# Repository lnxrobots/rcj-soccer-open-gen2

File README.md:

# RoboCup Soccer Open, Gen 2

## Setup

### Clone

Clone this repository in the home directory.

### Enable SSH and UART

Using `sudo raspi-config`

### Install packages and libraries

```
sudo apt install python3-pip git i2c-tools python3-opencv python3-serial python3-websockets
```

```
pip3 install bluedot
```

### Set cameras and optionally disable builtin Bluetooth

Add following lines to `/boot/firmware/config.txt`, change cameras if needed:

```
# Automatically load overlays for detected cameras
camera_auto_detect=0
dtoverlay=imx708,rotation=0,cam0
dtoverlay=imx477,cam1

# Uncomment to disable builtin bluetooth - custom
#dtoverlay=disable-bt
```

### Add launcher to autostart

Run `Launcher/apply_service.sh`.

### Pairing robots

Pair using [bluedot manual](https://bluedot.readthedocs.io/en/latest/pairpipi.html).

### Camera

Obtain frames using [Picamera2](https://github.com/raspberrypi/picamera2).

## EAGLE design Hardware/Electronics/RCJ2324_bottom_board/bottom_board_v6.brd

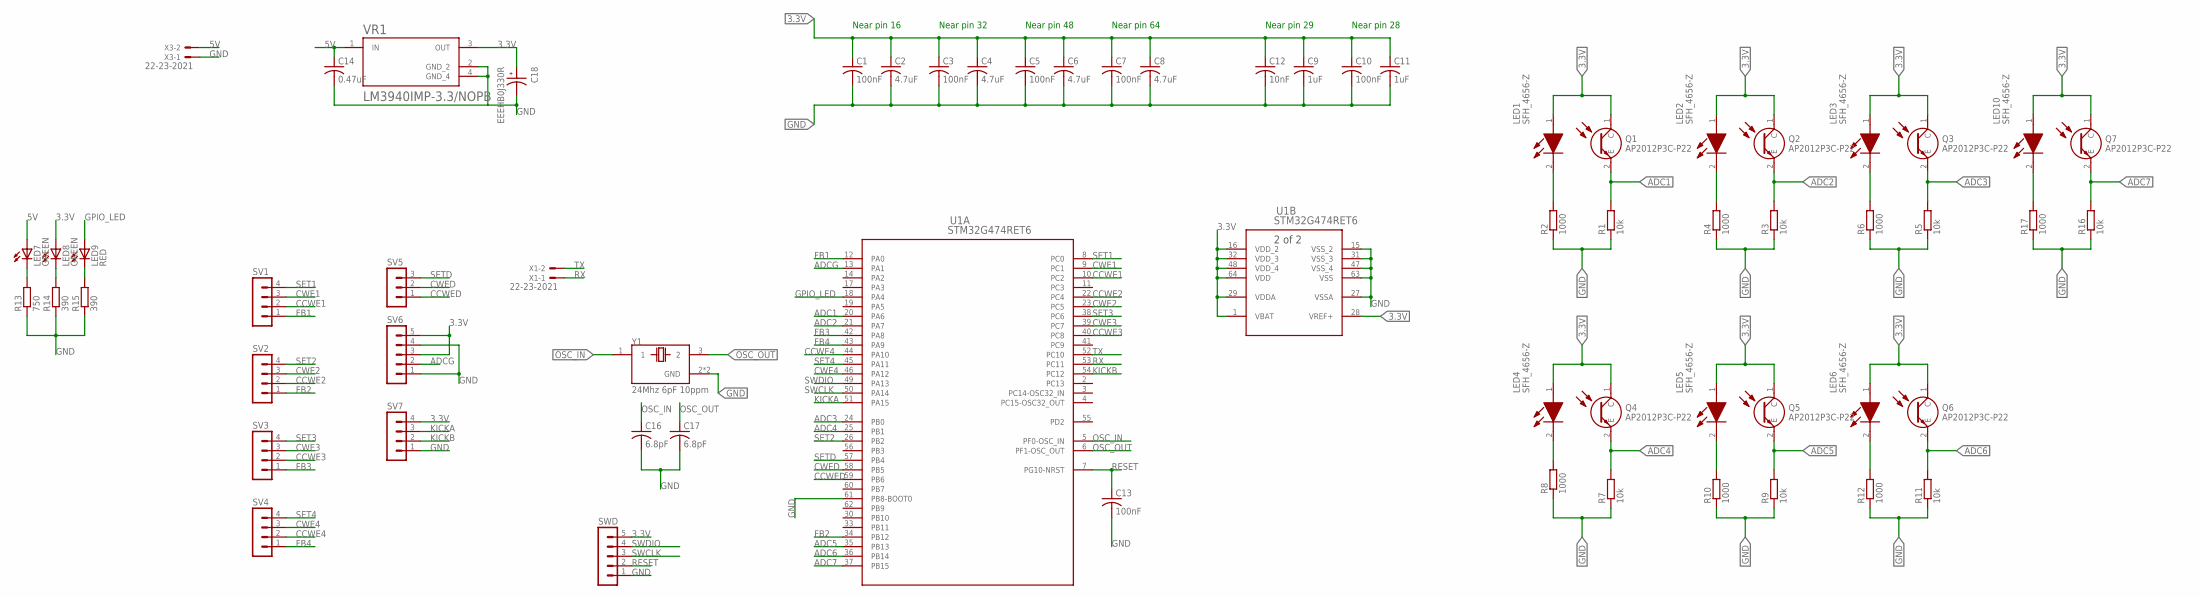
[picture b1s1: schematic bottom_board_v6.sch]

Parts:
C1, C3, C5, C7, C10, C13: 100nF; C0603
C2, C4, C6, C8: 4.7uF; C0603
C9, C11: 1uF; C0603
C12: 10nF; C0603
C14: 0.47uF; C0603
C16, C17: 6.8pF; C0603
C18: EEEHB0J330R; CAP_EEEHB0J330R
LED1, LED2, LED3, LED4, LED5, LED6, LED10: SFH_4656-Z; SFH4656Z
LED7, LED8: GREEN; CHIPLED_0603
LED9: RED; CHIPLED_0603
Q1, Q2, Q3, Q4, Q5, Q6, Q7: AP2012P3C-P22; AP2012P3CP22
R1, R3, R5, R7, R9, R11, R16: 10k; R0603
R2, R4, R6, R8, R10, R12, R17: 1000; R0603
R13: 750; R0603
R14, R15: 390; R0603
SV1, SV2, SV3, SV4, SV7: MA04-1
SV5: MA03-1
SV6: MA05-1
SWD: MA05-1
U1: STM32G474RET6; LQFP64-10X10MM
VR1: LM3940IMP-3.3/NOPB; VREG_LM3940IMP-3.3/NOPB
X1, X3: 22-23-2021
Y1: 24Mhz 6pF 10ppm; XTAL_TSX-3225_16.0000MF18X-AC3

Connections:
3.3V: C1.1, C2.1, C3.1, C4.1, C5.1, C6.1, C7.1, C8.1, C9.1, C10.1, C11.1, C12.1, C18.1, LED1.1 (A), LED2.1 (A), LED3.1 (A), LED4.1 (A), LED5.1 (A), LED6.1 (A), LED8.A, LED10.1 (A), Q1.1 (C), Q2.1 (C), Q3.1 (C), Q4.1 (C), Q5.1 (C), Q6.1 (C), Q7.1 (C), SV6.3, SV6.5, SV7.4, SWD.5, U1.1 (VBAT), U1.16 (VDD_2), U1.28 (VREF+), U1.29 (VDDA), U1.32 (VDD_3), U1.48 (VDD_4), U1.64 (VDD), VR1.3 (OUT)
5V: C14.1, LED7.A, VR1.1 (IN), X3.2
ADC1: Q1.2 (E), R1.2, U1.20 (PA6)
ADC2: Q2.2 (E), R3.2, U1.21 (PA7)
ADC3: Q3.2 (E), R5.2, U1.24 (PB0)
ADC4: Q4.2 (E), R7.2, U1.25 (PB1)
ADC5: Q5.2 (E), R9.2, U1.35 (PB13)
ADC6: Q6.2 (E), R11.2, U1.36 (PB14)
ADC7: Q7.2 (E), R16.2, U1.37 (PB15)
ADCG: SV6.2, U1.13 (PA1)
CCWE1: SV1.2, U1.10 (PC2)
CCWE2: SV2.2, U1.22 (PC4)
CCWE3: SV3.2, U1.40 (PC8)
CCWE4: SV4.2, U1.44 (PA10)
CCWED: SV5.1, U1.59 (PB6)
CWE1: SV1.3, U1.9 (PC1)
CWE2: SV2.3, U1.23 (PC5)
CWE3: SV3.3, U1.39 (PC7)
CWE4: SV4.3, U1.46 (PA12)
CWED: SV5.2, U1.58 (PB5)
FB1: SV1.1, U1.12 (PA0)
FB2: SV2.1, U1.34 (PB12)
FB3: SV3.1, U1.42 (PA8)
FB4: SV4.1, U1.43 (PA9)
GND: C1.2, C2.2, C3.2, C4.2, C5.2, C6.2, C7.2, C8.2, C9.2, C10.2, C11.2, C12.2, C13.2, C14.2, C16.2, C17.2, C18.2, R1.1, R2.1, R3.1, R4.1, R5.1, R6.1, R7.1, R8.1, R9.1, R10.1, R11.1, R12.1, R13.1, R14.1, R15.1, R16.1, R17.1, SV6.1, SV6.4, SV7.1, SWD.1, U1.15 (VSS_2), U1.27 (VSSA), U1.31 (VSS_3), U1.47 (VSS_4), U1.61 (PB8-BOOT0), U1.63 (VSS), VR1.2 (GND_2), VR1.4 (GND_4), X3.1, Y1.2 (GND), Y1.4 (GND)
GPIO_LED: LED9.A, U1.18 (PA4)
KICKA: SV7.3, U1.51 (PA15)
KICKB: SV7.2, U1.54 (PC12)
unnamed: LED2.2 (K), R4.2
unnamed: LED3.2 (K), R6.2
unnamed: LED1.2 (K), R2.2
unnamed: LED4.2 (K), R8.2
unnamed: LED5.2 (K), R10.2
unnamed: LED6.2 (K), R12.2
unnamed: LED7.C, R13.2
unnamed: LED8.C, R14.2
unnamed: LED9.C, R15.2
unnamed: LED10.2 (K), R17.2
OSC_IN: C16.1, U1.5 (PF0-OSC_IN), Y1.1
OSC_OUT: C17.1, U1.6 (PF1-OSC_OUT), Y1.3 (2)
RESET: C13.1, SWD.2, U1.7 (PG10-NRST)
RX: U1.53 (PC11), X1.1
SET1: SV1.4, U1.8 (PC0)
SET2: SV2.4, U1.26 (PB2)
SET3: SV3.4, U1.38 (PC6)
SET4: SV4.4, U1.45 (PA11)
SETD: SV5.3, U1.57 (PB4)
SWCLK: SWD.3, U1.50 (PA14)
SWDIO: SWD.4, U1.49 (PA13)
TX: U1.52 (PC10), X1.2

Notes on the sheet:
Near pin 16
Near pin 32
Near pin 48
Near pin 64
Near pin 29
Near pin 28

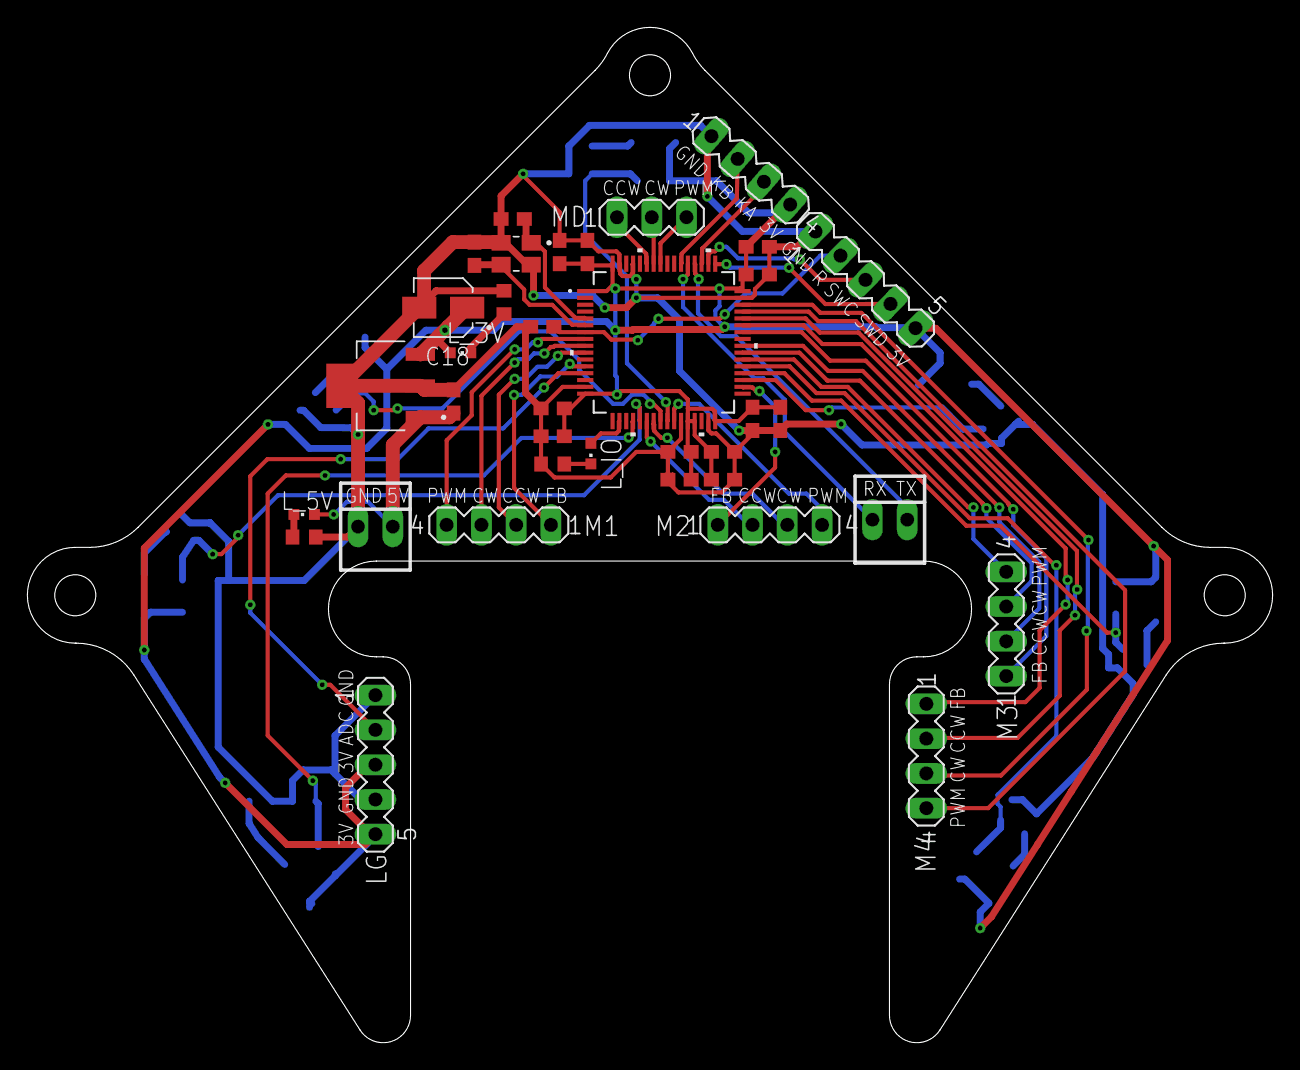
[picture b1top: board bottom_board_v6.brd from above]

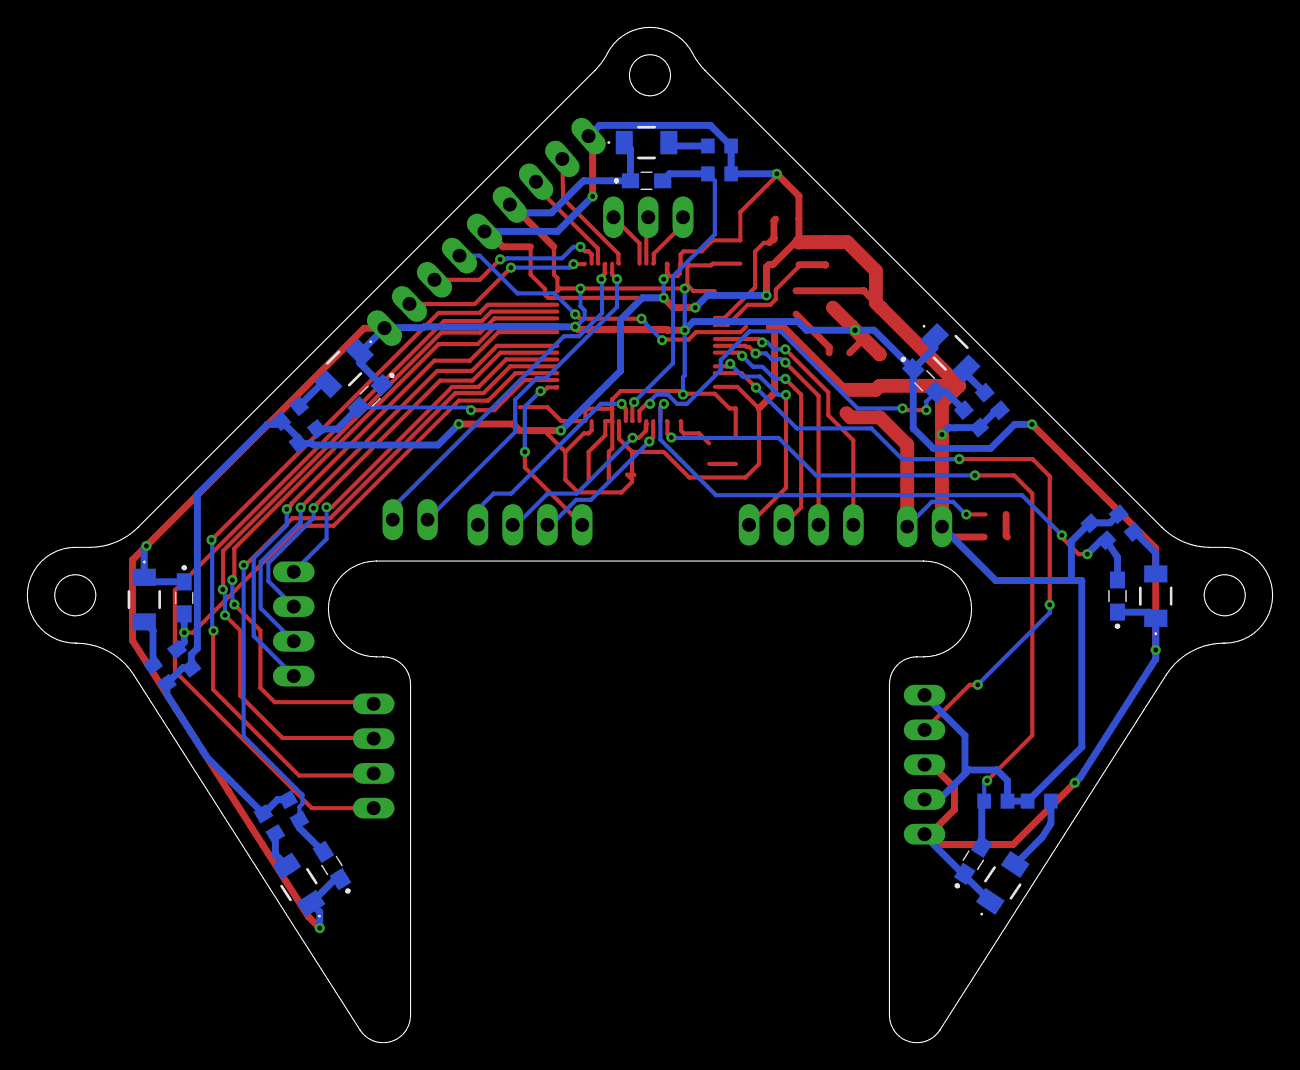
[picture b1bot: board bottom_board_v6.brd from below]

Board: 2 copper layers, 91.0 x 74.2 mm, 64 parts (28 on the bottom side), 50 nets.

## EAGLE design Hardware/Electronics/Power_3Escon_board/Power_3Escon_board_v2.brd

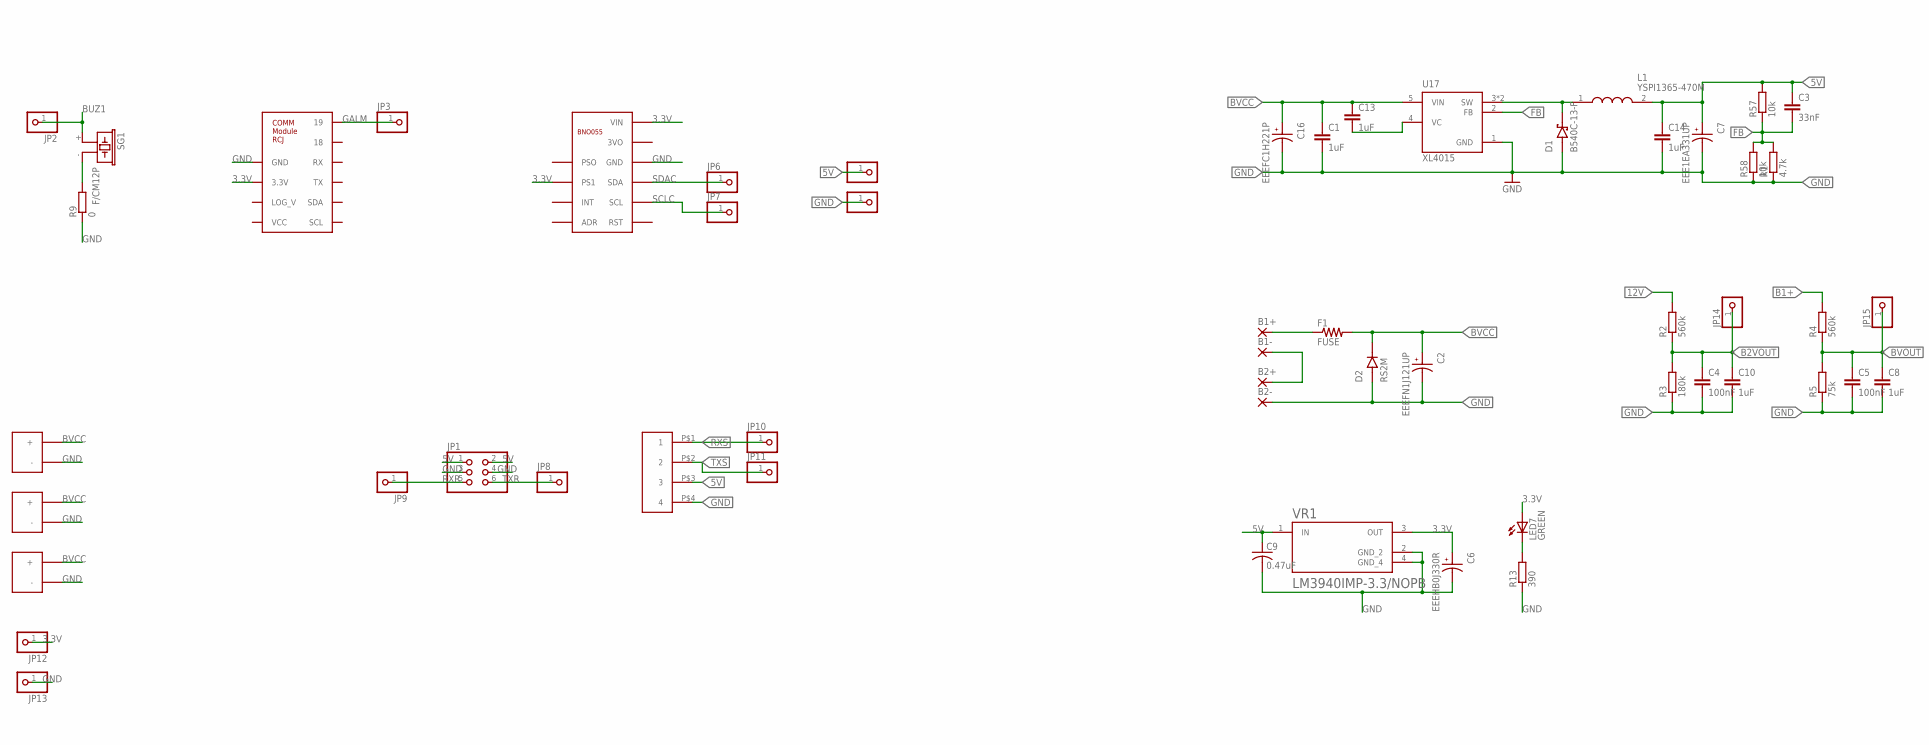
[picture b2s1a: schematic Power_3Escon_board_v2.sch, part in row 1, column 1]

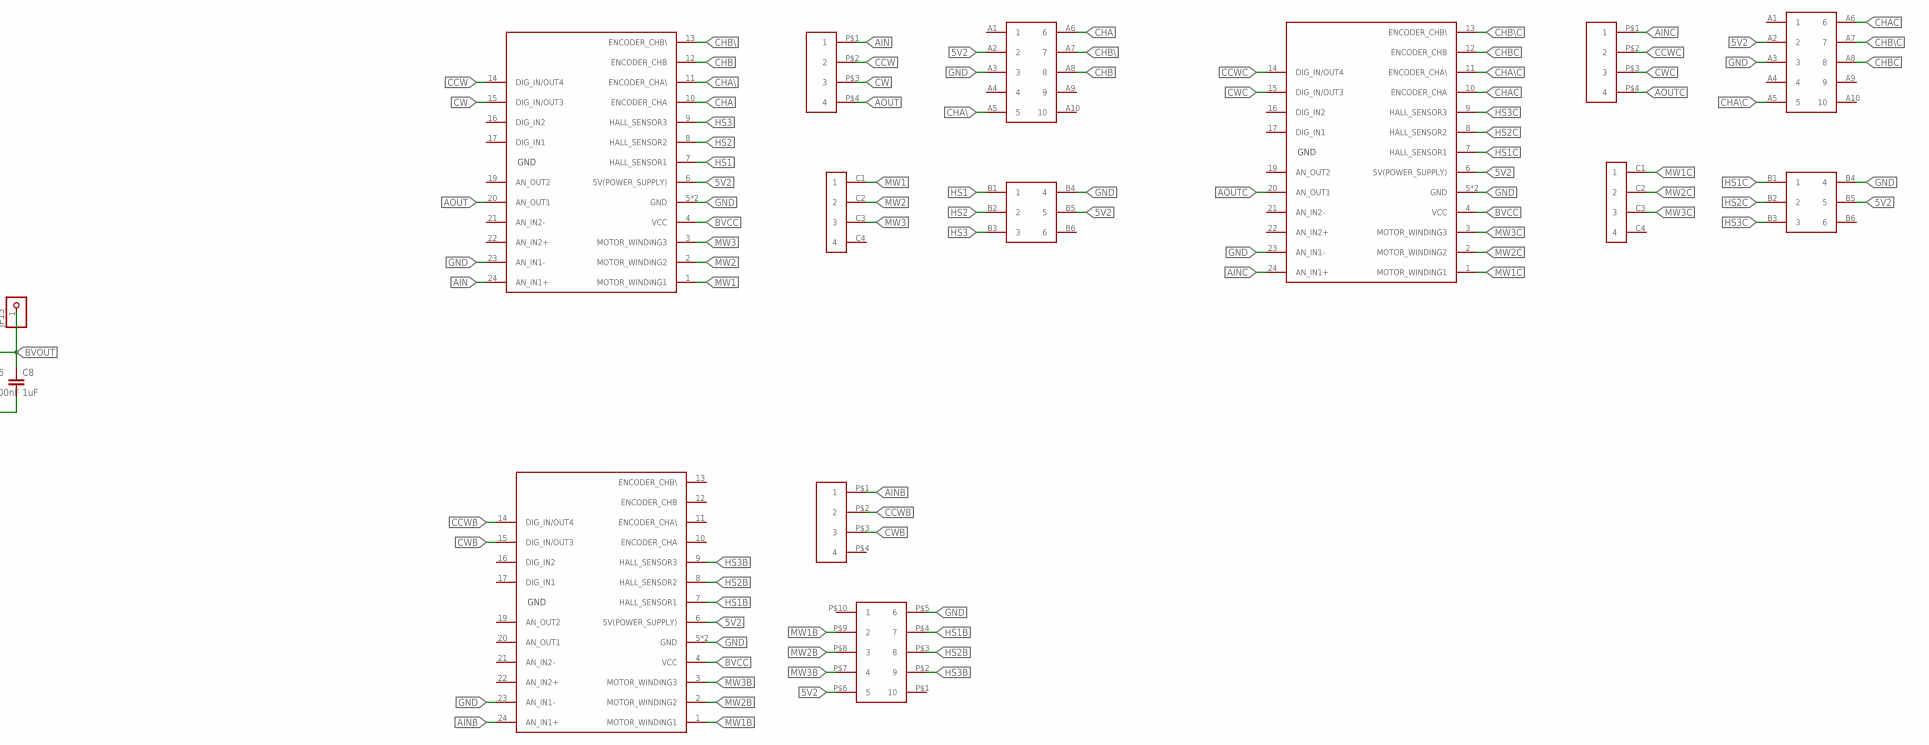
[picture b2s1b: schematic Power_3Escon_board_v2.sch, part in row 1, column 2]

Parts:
B1+, B1-, B2+, B2-: 3,81/1,4
C1, C8, C10, C13, C14: 1uF; C0603
C2: EEEFN1J121UP; CAP_EEEFN1J121UP
C3: 33nF; C0603
C4, C5: 100nF; C0603
C6: EEEHB0J330R; CAP_EEEHB0J330R
C7: EEE1EA331UP; CAP_EEE1EA331UP
C9: 0.47uF; C0603
C16: EEEFC1H221P; CAP_EEEFC1H221P
D1: B540C-13-F; DIOM6959X245N
D2: RS2M; DIOM4336X265N
F1: FUSE; R1206
JP1: PINHD-2X3; 2X03
JP2, JP3, JP4, JP5, JP6, JP7, JP8, JP9, JP10, JP11, JP12, JP13, JP14, JP15: PINHD-1X1; 1X01
L1: YSPI1365-470M; INDPM138126X650N
LED7: GREEN; CHIPLED_0603
R1: 4.7k; R0603
R2, R4: 560k; R0603
R3: 180k; R0603
R5: 75k; R0603
R9: 0; R0603
R13: 390; R0603
R57, R58: 10k; R0603
SG1: F/CM12P
U17: XL4015; CONV_XL4015
U$1, U$10, U$15: ESCON24/224/2; ESCON24/2
U$2: GAL_MODULE
U$3: BNO055
U$4, U$13, U$16, U$22: 280378-2CONNECTOR
U$5, U$17: PIN2.54-2X5
U$6, U$18: MX-44914-0601
U$7, U$19: MX5566
U$14: 2,5MSF10
U$23, U$24, U$25: SVORKOVNICA3.5_P2; SVORKOVNICA3.5
VR1: LM3940IMP-3.3/NOPB; VREG_LM3940IMP-3.3/NOPB

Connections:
3.3V: C6.1, JP12.1, LED7.A, U$2.3.3V, U$3.PS1, U$3.VIN, VR1.3 (OUT)
5V: C3.1, C7.1, C9.1, C14.1, JP1.1, JP1.2, JP4.1, L1.2, R57.2, U$22.P$3 (3), VR1.1 (IN)
5V2: U$1.6 (5V(POWER_SUPPLY)), U$5.A2 (2), U$6.B5 (5), U$10.6 (5V(POWER_SUPPLY)), U$14.P$6 (5), U$15.6 (5V(POWER_SUPPLY)), U$17.A2 (2), U$18.B5 (5)
12V: B1-.1, B2+.1, R2.2
AIN: U$1.24 (AN_IN1+), U$4.P$1 (1)
AINB: U$10.24 (AN_IN1+), U$13.P$1 (1)
AINC: U$15.24 (AN_IN1+), U$16.P$1 (1)
AOUT: U$1.20 (AN_OUT1), U$4.P$4 (4)
AOUTC: U$15.20 (AN_OUT1), U$16.P$4 (4)
B1+: B1+.1, F1.1, R4.2
B2VOUT: C4.1, C10.1, JP14.1, R2.1, R3.2
BUZ1: JP2.1, SG1.+ (1)
BVCC: C1.1, C2.1, C13.1, C16.1, D2.C (K), F1.2, U17.5 (VIN), U$1.4 (VCC), U$10.4 (VCC), U$15.4 (VCC), U$23.P$1 (+), U$24.P$1 (+), U$25.P$1 (+)
BVOUT: C5.1, C8.1, JP15.1, R4.1, R5.2
CCW: U$1.14 (DIG_IN/OUT4), U$4.P$2 (2)
CCWB: U$10.14 (DIG_IN/OUT4), U$13.P$2 (2)
CCWC: U$15.14 (DIG_IN/OUT4), U$16.P$2 (2)
CHA: U$1.10 (ENCODER_CHA), U$5.A6 (6)
CHAC: U$15.10 (ENCODER_CHA), U$17.A6 (6)
CHA\\: U$1.11 (ENCODER_CHA\\), U$5.A5 (5)
CHA\\C: U$15.11 (ENCODER_CHA\\), U$17.A5 (5)
CHB: U$1.12 (ENCODER_CHB), U$5.A8 (8)
CHBC: U$15.12 (ENCODER_CHB), U$17.A8 (8)
CHB\\: U$1.13 (ENCODER_CHB\\), U$5.A7 (7)
CHB\\C: U$15.13 (ENCODER_CHB\\), U$17.A7 (7)
CW: U$1.15 (DIG_IN/OUT3), U$4.P$3 (3)
CWB: U$10.15 (DIG_IN/OUT3), U$13.P$3 (3)
CWC: U$15.15 (DIG_IN/OUT3), U$16.P$3 (3)
FB: C3.2, R1.2, R57.1, R58.2, U17.2 (FB)
GALM: JP3.1, U$2.19
GND: B2-.1, C1.2, C2.2, C4.2, C5.2, C6.2, C7.2, C8.2, C9.2, C10.2, C14.2, C16.2, D1.A, D2.A, JP1.3, JP1.4, JP5.1, JP13.1, R1.1, R3.1, R5.1, R9.1, R13.1, R58.1, U17.1 (GND), U$1.5 (GND), U$1.18 (GND), U$1.23 (AN_IN1-), U$2.GND, U$3.GND, U$5.A3 (3), U$6.B4 (4), U$10.5 (GND), U$10.18 (GND), U$10.23 (AN_IN1-), U$14.P$5 (6), U$15.5 (GND), U$15.18 (GND), U$15.23 (AN_IN1-), U$17.A3 (3), U$18.B4 (4), U$22.P$4 (4), U$23.P$2 (-), U$24.P$2 (-), U$25.P$2 (-), VR1.2 (GND_2), VR1.4 (GND_4)
HS1: U$1.7 (HALL_SENSOR1), U$6.B1 (1)
HS1B: U$10.7 (HALL_SENSOR1), U$14.P$4 (7)
HS1C: U$15.7 (HALL_SENSOR1), U$18.B1 (1)
HS2: U$1.8 (HALL_SENSOR2), U$6.B2 (2)
HS2B: U$10.8 (HALL_SENSOR2), U$14.P$3 (8)
HS2C: U$15.8 (HALL_SENSOR2), U$18.B2 (2)
HS3: U$1.9 (HALL_SENSOR3), U$6.B3 (3)
HS3B: U$10.9 (HALL_SENSOR3), U$14.P$2 (9)
HS3C: U$15.9 (HALL_SENSOR3), U$18.B3 (3)
MW1: U$1.1 (MOTOR_WINDING1), U$7.C1 (1)
MW1B: U$10.1 (MOTOR_WINDING1), U$14.P$9 (2)
MW1C: U$15.1 (MOTOR_WINDING1), U$19.C1 (1)
MW2: U$1.2 (MOTOR_WINDING2), U$7.C2 (2)
MW2B: U$10.2 (MOTOR_WINDING2), U$14.P$8 (3)
MW2C: U$15.2 (MOTOR_WINDING2), U$19.C2 (2)
MW3: U$1.3 (MOTOR_WINDING3), U$7.C3 (3)
MW3B: U$10.3 (MOTOR_WINDING3), U$14.P$7 (4)
MW3C: U$15.3 (MOTOR_WINDING3), U$19.C3 (3)
unnamed: LED7.C, R13.2
unnamed: C13.2, U17.4 (VC)
unnamed: R9.2, SG1.- (2)
unnamed: D1.C (K), L1.1, U17.3 (SW), U17.3.1 (SW)
RXR: JP1.5, JP9.1
RXS: JP10.1, U$22.P$1 (1)
SCLC: JP7.1, U$3.SCL
SDAC: JP6.1, U$3.SDA
TXR: JP1.6, JP8.1
TXS: JP11.1, U$22.P$2 (2)

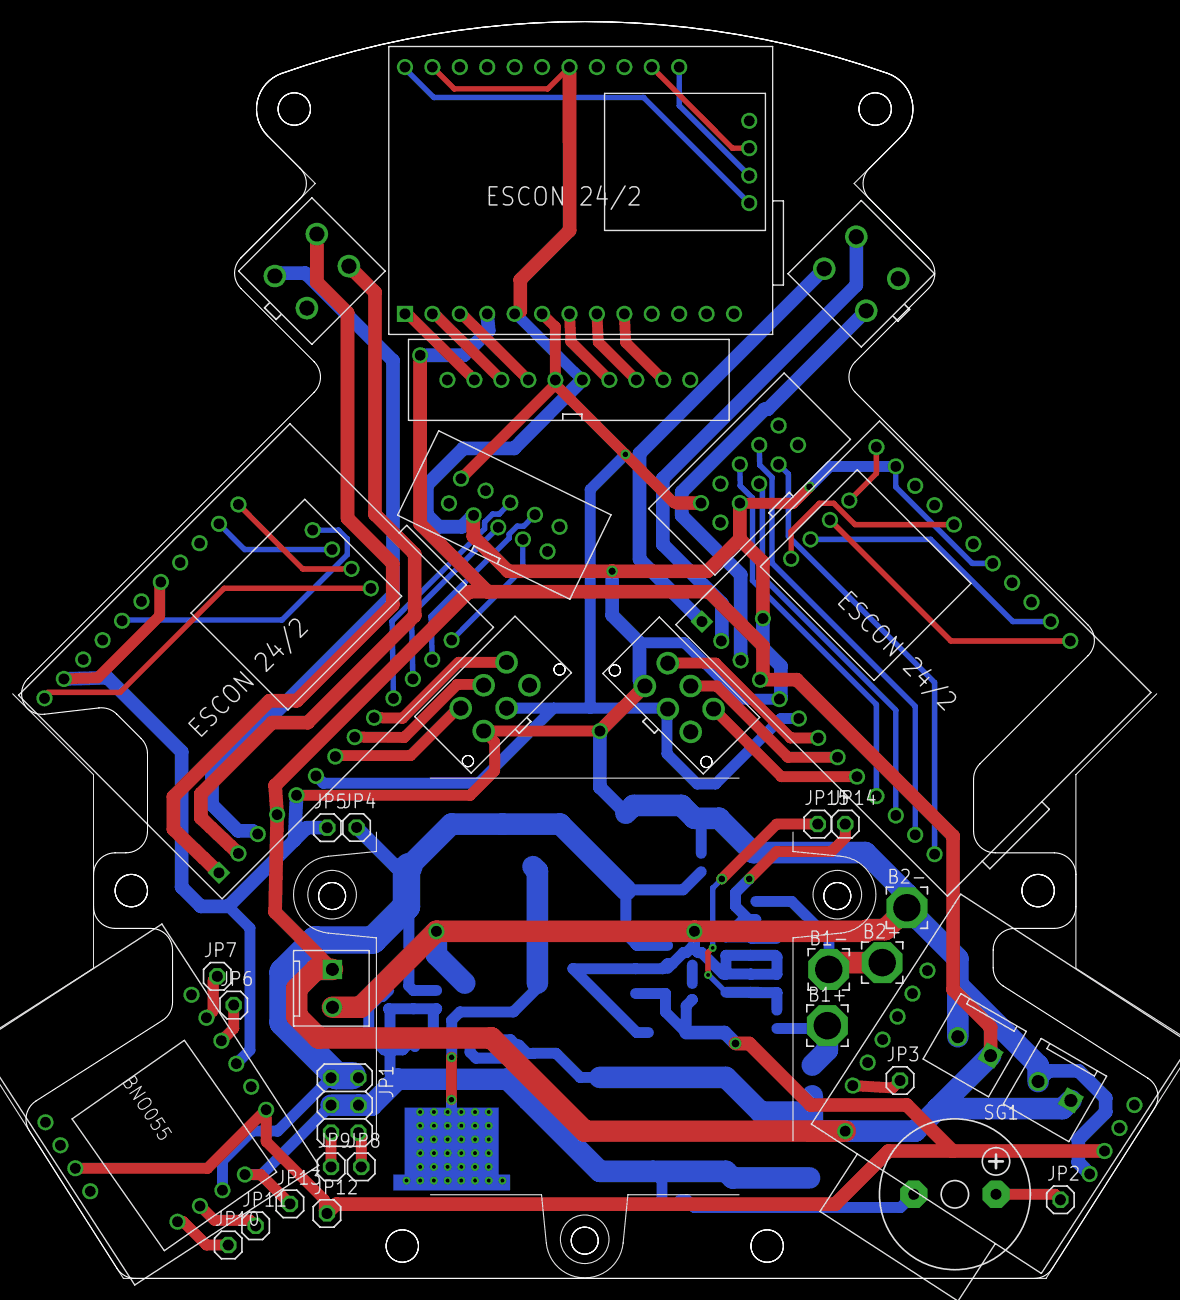
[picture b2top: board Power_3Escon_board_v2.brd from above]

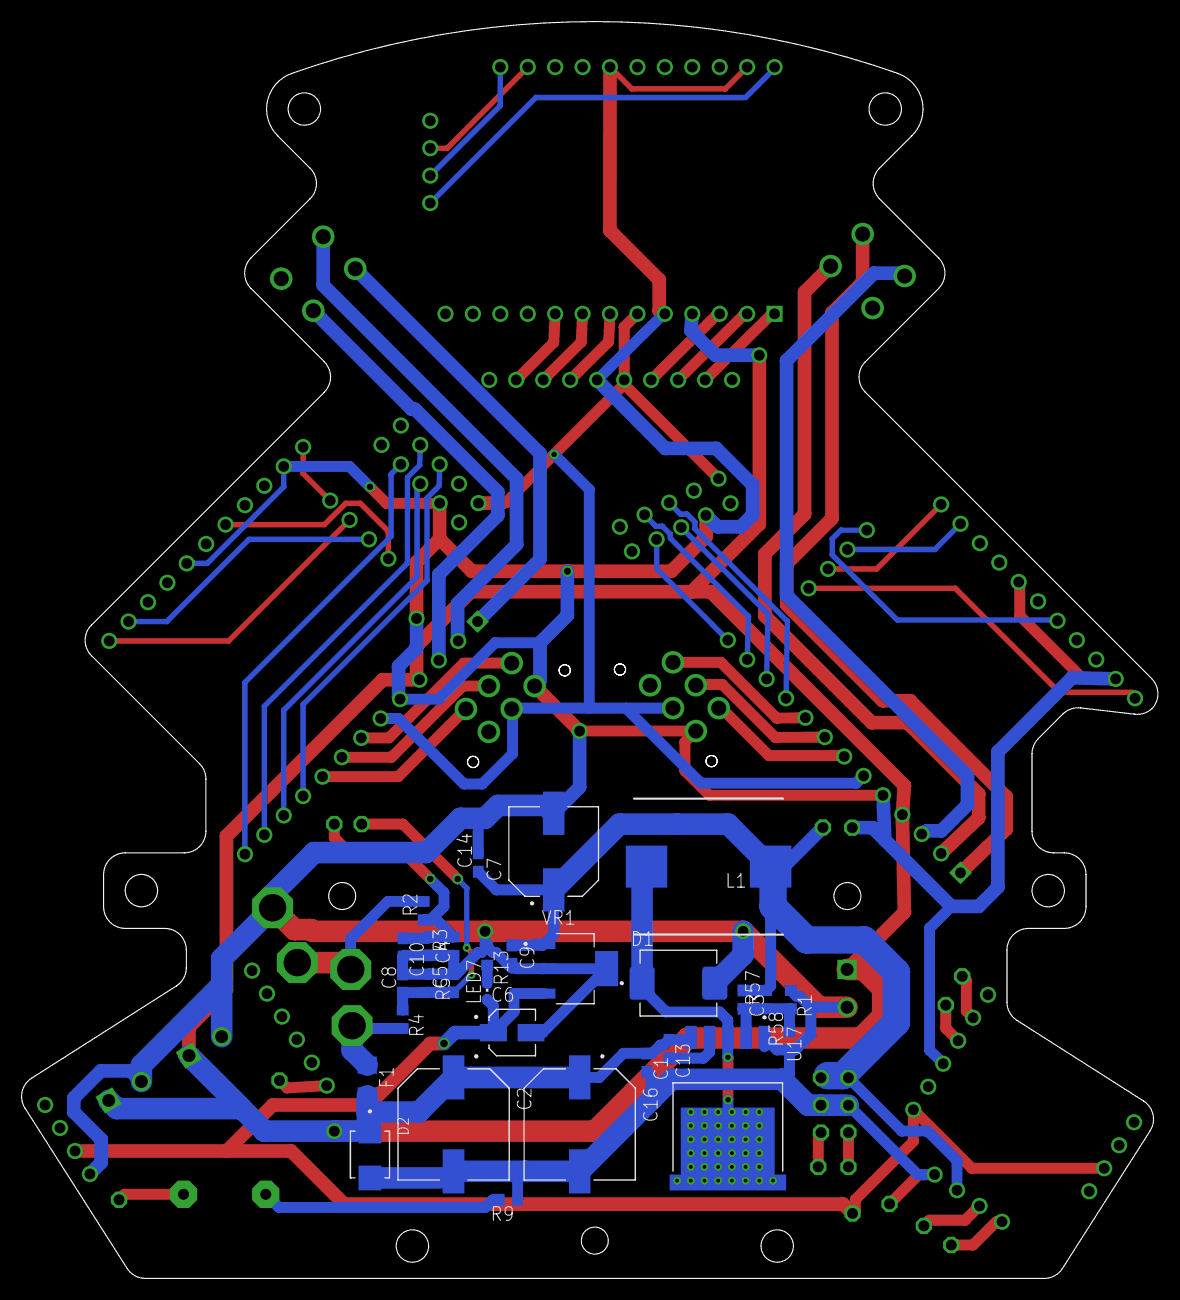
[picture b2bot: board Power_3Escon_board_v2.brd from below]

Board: 2 copper layers, 105.3 x 116.4 mm, 68 parts (29 on the bottom side), 59 nets.

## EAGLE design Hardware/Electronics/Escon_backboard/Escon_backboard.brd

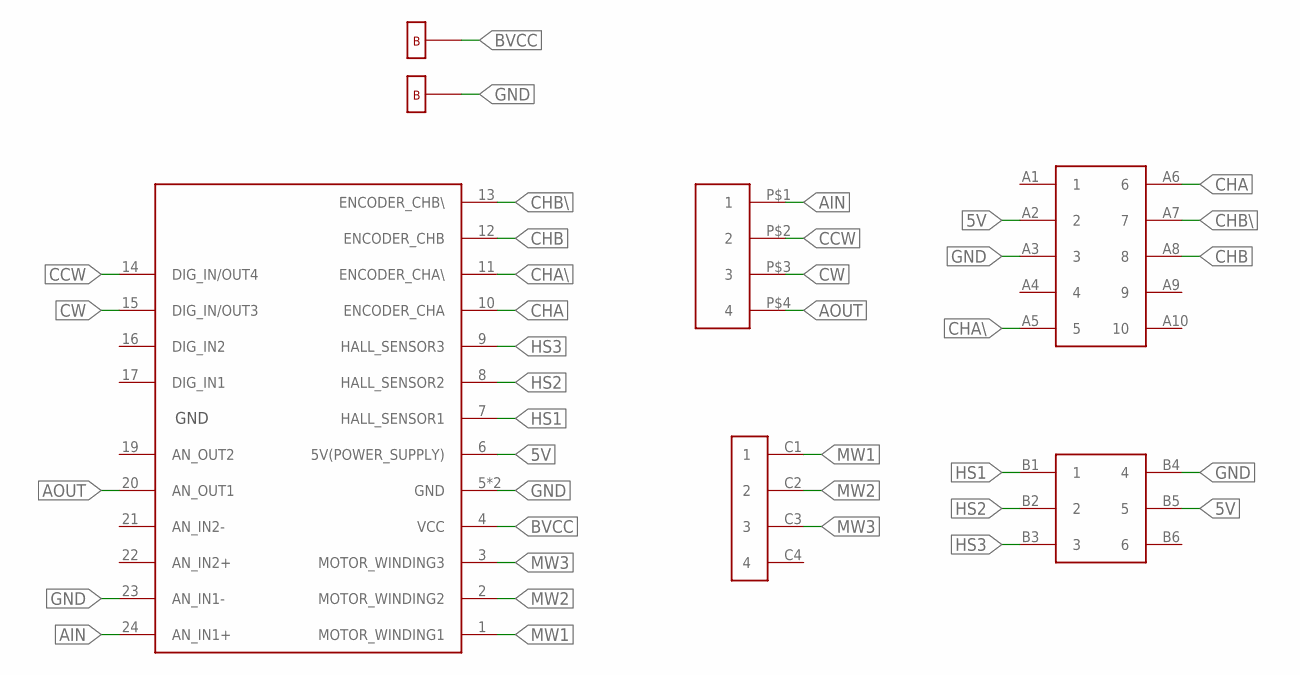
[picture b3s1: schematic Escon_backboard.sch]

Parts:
U$1: ESCON24/224/2; ESCON24/2
U$2: 280378-2CONNECTOR
U$3: PIN2.54-2X5
U$4: MX-44914-0601
U$5: MX5566
U$6, U$7: BHOLE

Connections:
5V: U$1.6 (5V(POWER_SUPPLY)), U$3.A2 (2), U$4.B5 (5)
AIN: U$1.24 (AN_IN1+), U$2.P$1 (1)
AOUT: U$1.20 (AN_OUT1), U$2.P$4 (4)
BVCC: U$1.4 (VCC), U$6.P$1
CCW: U$1.14 (DIG_IN/OUT4), U$2.P$2 (2)
CHA: U$1.10 (ENCODER_CHA), U$3.A6 (6)
CHA\\: U$1.11 (ENCODER_CHA\\), U$3.A5 (5)
CHB: U$1.12 (ENCODER_CHB), U$3.A8 (8)
CHB\\: U$1.13 (ENCODER_CHB\\), U$3.A7 (7)
CW: U$1.15 (DIG_IN/OUT3), U$2.P$3 (3)
GND: U$1.5 (GND), U$1.18 (GND), U$1.23 (AN_IN1-), U$3.A3 (3), U$4.B4 (4), U$7.P$1
HS1: U$1.7 (HALL_SENSOR1), U$4.B1 (1)
HS2: U$1.8 (HALL_SENSOR2), U$4.B2 (2)
HS3: U$1.9 (HALL_SENSOR3), U$4.B3 (3)
MW1: U$1.1 (MOTOR_WINDING1), U$5.C1 (1)
MW2: U$1.2 (MOTOR_WINDING2), U$5.C2 (2)
MW3: U$1.3 (MOTOR_WINDING3), U$5.C3 (3)

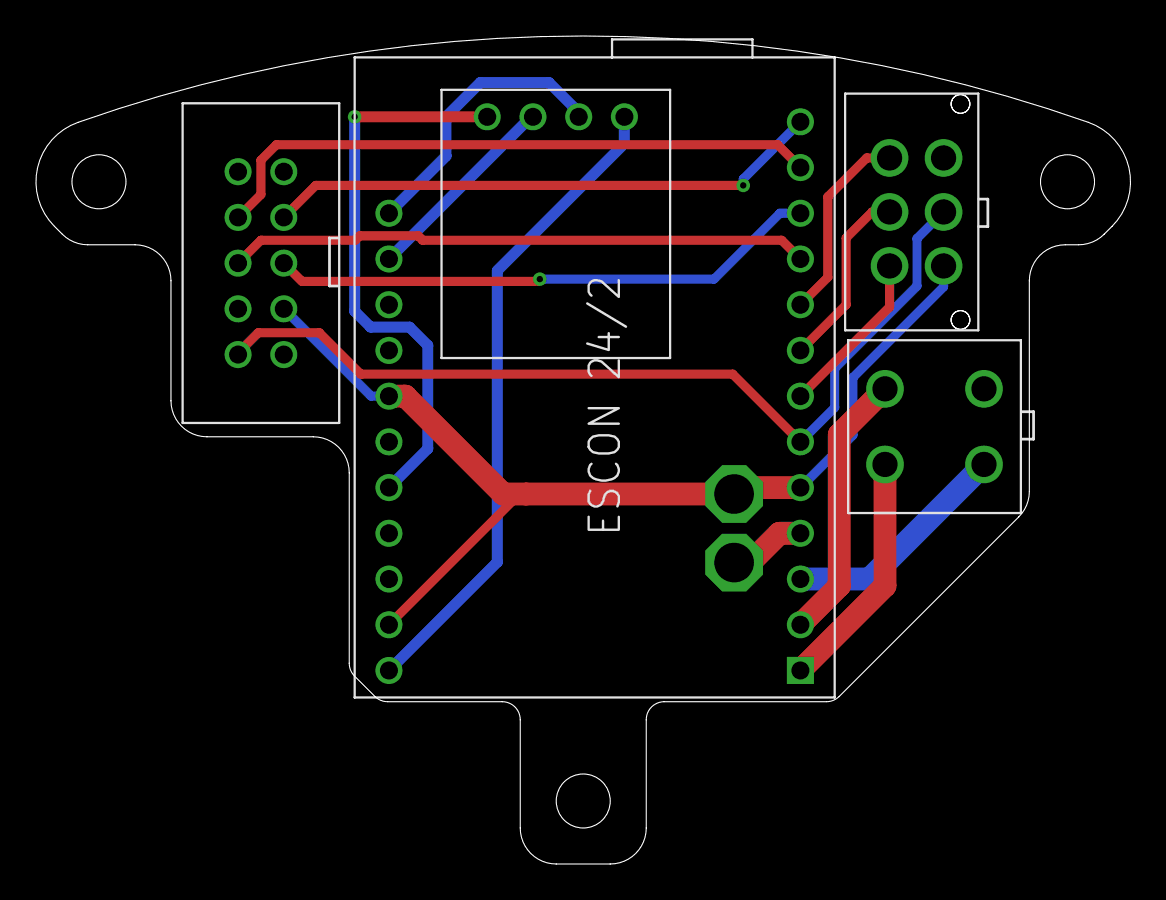
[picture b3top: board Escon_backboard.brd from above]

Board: 2 copper layers, 60.8 x 46.0 mm, 7 parts (0 on the bottom side), 17 nets.

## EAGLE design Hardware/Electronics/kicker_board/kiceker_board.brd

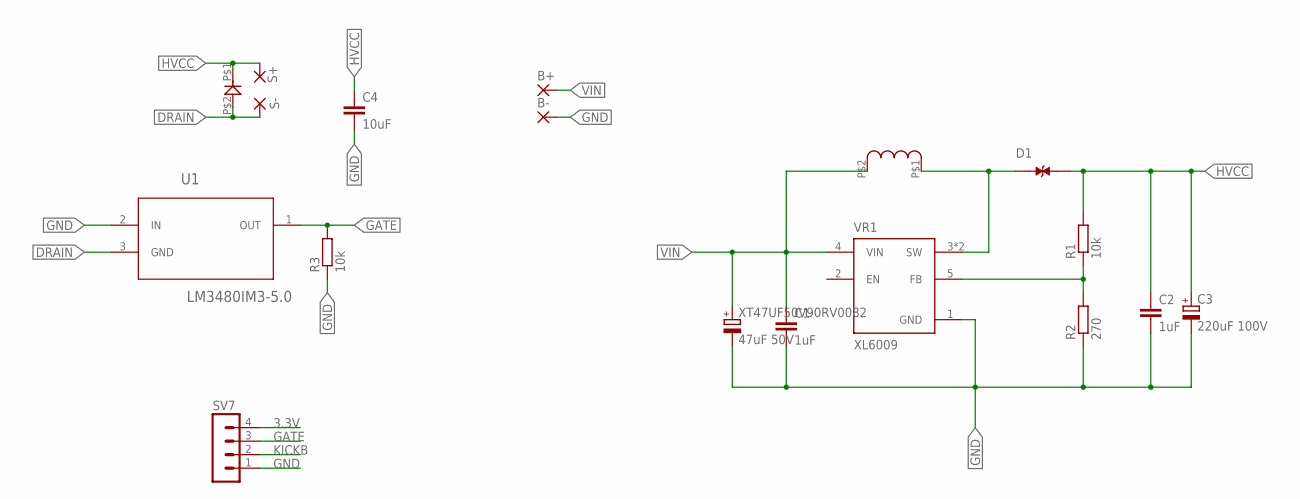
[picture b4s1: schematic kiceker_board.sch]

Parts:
B+: 3,81/1,4
B-: 3,81/1,4
C1, C2: 1uF; C0603
C3: 220uF 100V; E5-5
C4: 10uF; C0603
D1: SMCJ15CA_V7G; DIOM6859X262N
R1, R3: 10k; R0603
R2: 270; R0603
S+: 3,81/1,4
S-: 3,81/1,4
SV7: MA04-1
U1: LM3480IM3-5.0; SOT95P263X110-3N
U$1: TMPC1265
U$2: SMBF
VR1: XL6009; DPAK170P1435X465-6N
XT47UF50V90RV0082: 47uF 50V; 153CLV-0605

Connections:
3.3V: SV7.4
DRAIN: S-.1, U1.3 (GND), U$2.P$2
GATE: R3.2, SV7.3, U1.1 (OUT)
GND: B-.1, C1.2, C2.2, C3.-, C4.2, R2.1, R3.1, SV7.1, U1.2 (IN), VR1.1 (GND), XT47UF50V90RV0082.-
HVCC: C2.1, C3.+, C4.1, D1.2, R1.2, S+.1, U$2.P$1
KICKB: SV7.2
unnamed: D1.1, U$1.P$1, VR1.3 (SW), VR1.6 (SW)
unnamed: R1.1, R2.2, VR1.5 (FB)
VIN: B+.1, C1.1, U$1.P$2, VR1.4 (VIN), XT47UF50V90RV0082.+

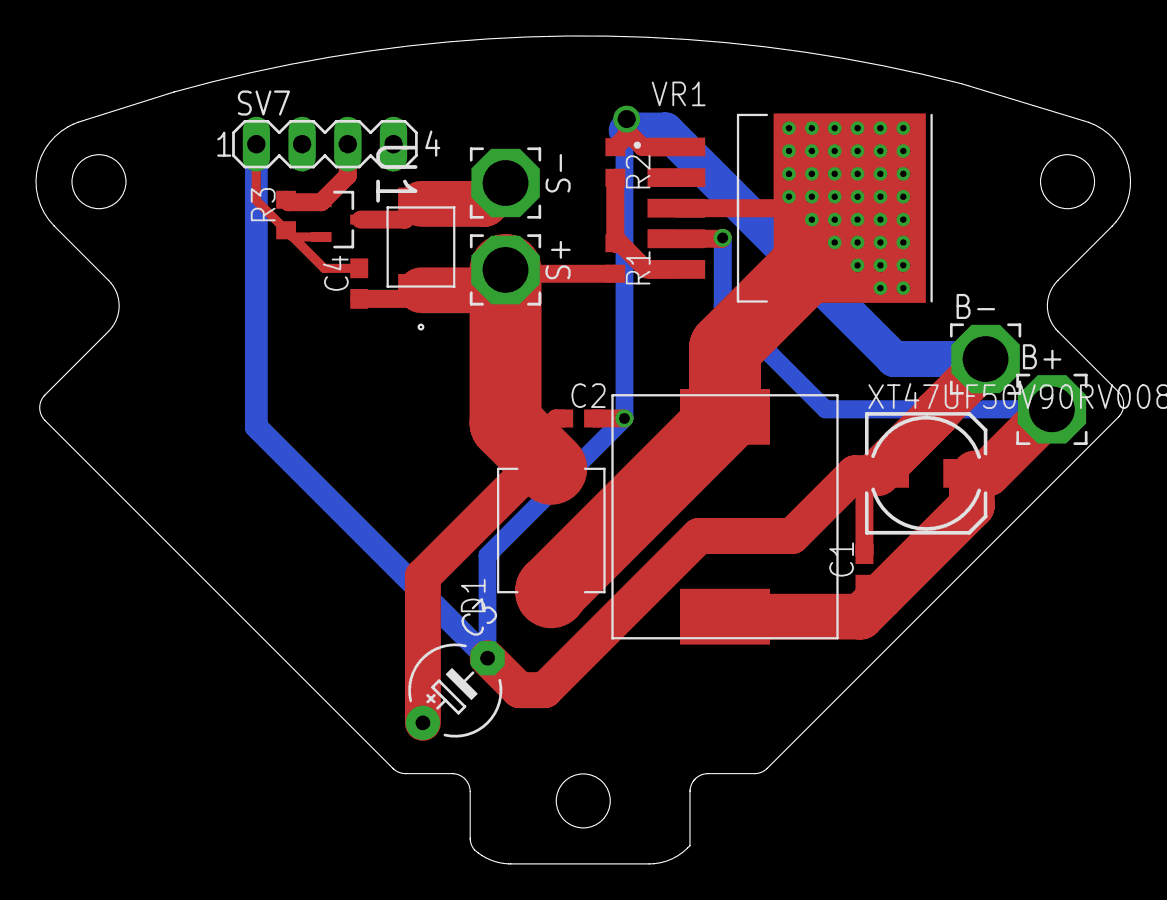
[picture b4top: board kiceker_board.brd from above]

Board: 2 copper layers, 60.8 x 46.0 mm, 18 parts (0 on the bottom side), 7 nets.

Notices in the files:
parts and their libraries:
COPYRIGHT: Copyright (C) 2023 Ultra Librarian. All rights reserved.
